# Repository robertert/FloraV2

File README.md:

# Doniczka-robot

Autonomiczna, solarna, mobilna doniczka: jezdzi po trawniku za sloncem, mierzy
warunki i sama podlewa rosline. Praca inzynierska AGH, termin styczen 2027.

## Uklad repozytorium

Jedno repo, dwie jednostki polaczone UART-em przez maszt, wspolne sterowniki.

```
components/        sterowniki dzielone przez obie jednostki
  flora_board/     mapa pinow bryly + przeliczniki odometrii
  flora_motors/    naped na Cytron MDD10A (PWM + DIR)
  flora_encoders/  enkodery kwadraturowe na PCNT
  flora_ina226/    pomiar pradu i napiecia szyny 12V
  flora_msgs/      kontrakt wiadomosci UART (wspolny dla obu stron)
hub/               BRYLA: ESP32-S3 DevKitC-1 N16R8
                   naped, odometria, zasilanie, podlewanie, telemetria
node/              GLOWICA MASZTU: ESP32-S3 z gniazdem kamery (do kupienia)
                   kompas sloneczny, BME280, IMU, czujnik deszczu
```

Nazwy katalogow `hub` i `node` pochodza z wczesniejszej wersji projektu.
`hub` to jednostka DOLNA, `node` to GLOWICA.

Wspolne komponenty trafiaja do obu projektow przez `EXTRA_COMPONENT_DIRS`
ustawione w `CMakeLists.txt` kazdej jednostki.

## Wymagania

ESP-IDF **v6.1**, zainstalowane przez EIM w `~/.espressif/v6.1/esp-idf`.
Obie jednostki to ESP32-S3.

## Praca z projektem

`./dev.sh` sam wciaga srodowisko ESP-IDF i wykrywa port, wiec nie trzeba
niczego sourcowac:

```sh
./dev.sh hub build      # zbuduj bryle
./dev.sh hub fm         # build + flash + monitor, najczestszy cykl
./dev.sh hub monitor    # sama konsola, wyjscie Ctrl+]
./dev.sh hub menuconfig
./dev.sh ports          # co widac na USB
./dev.sh help           # pelna lista komend
```

Nieznane komendy leca wprost do `idf.py`, np. `./dev.sh hub partition-table`.

Przy dwoch podlaczonych plytkach trzeba wskazac port:
`FLORA_PORT=/dev/cu.usbmodem101 ./dev.sh hub fm`.

## Debug przez MQTT

Bryla publikuje wszystko, co do niej dociera (wlasne czujniki i wiadomosci
glowicy), pod `flora/robot1/tele/*` i `flora/robot1/head/*`, a komendy
przyjmuje z `flora/robot1/cmd/*` (opis w `hub/main/hub_remote.h`).

1. Broker na Macu (`brew install mosquitto`):
   `mosquitto -c tools/dashboard/mosquitto.conf -v`
2. Adres brokera dla robota to IP Maca w tej samej sieci:
   `FLORA_MQTT_URI_DEFAULT` w `flora_board.h` albo klucz `mqtt_uri` w NVS.
3. Panel: otworz `tools/dashboard/index.html` w przegladarce, adres
   `ws://<ip-maca>:9001`. Strzalki na klawiaturze jada, spacja to STOP.
4. Z terminala: `mosquitto_sub -t 'flora/robot1/#' -v`,
   `mosquitto_pub -t flora/robot1/cmd/pump -m on`.

Naped z panelu staje sam po 1,5 s bez odswiezenia komendy (dead-man),
wiec zerwane WiFi nie zostawi jadacego robota.

**Do jakiego brokera laczy sie robot** - po kolei, az ktorys odpowie:

1. ustawienia z NVS (zmieniane zdalnie, patrz nizej),
2. serwer wkompilowany w firmware (`FLORA_MQTT_URI_DEFAULT` w `flora_board.h`,
   TLS, login `robot1`, haslo z NVS - w kodzie go nie ma),
3. broker na Macu po nazwie mDNS (`Roberts-MacBook-Pro.local`), bez hasel.

Haslo brokera trzeba wpisac raz (`cmd/config/mqtt_pass`, z lokalnego panelu,
gdy robot jest na brokerze Maca). Przezywa zwykle flashowanie, znika dopiero
po `erase-flash`.

**Ustawienia zdalnie** (karta "Ustawienia" w panelu albo z terminala), zapis
do NVS, siec i broker dzialaja po restarcie:

```sh
mosquitto_pub -t flora/robot1/cmd/config/mqtt_uri -m mqtt://172.20.10.14:1883
mosquitto_pub -t flora/robot1/cmd/reboot -m 1
```

Klucze: `wifi_ssid`, `wifi_pass`, `mqtt_uri`, `mqtt_user`, `mqtt_pass`,
`soil_dry`, `soil_wet`; wartosc `-` kasuje ustawienie. Zly adres albo haslo
w NVS nie wymaga podlaczania kabla - robot przejdzie do kolejnych prob.

**Diagnostyka zdalna** (`hub/main/hub_diag.c`):

- `tele/log` - ostrzezenia i bledy z logu ESP (poziomy W i E). Kolejka
  trzyma je takze bez polaczenia, wiec bledy z uruchamiania i z przerwy w
  sieci wychodza po polaczeniu. Konsola USB dostaje wszystko jak dotad.
- `tele/boot` (retain) - wersja firmware, data budowania, powod ostatniego
  restartu (`panic`, `task_wdt`, `brownout`... = awaria) i licznik startow.

Wersja firmware pochodzi z tagu `hub-vX.Y.Z` (`git tag hub-v0.1.0`); bez
niego jest skrot commita. Tagi `server-v...` sa dla serwera i do firmware
nie trafiaja.

**Historia** (Telegraf + InfluxDB + Grafana w Dockerze):

```sh
cd tools/telemetry && docker compose up -d
```

Grafana pod http://localhost:3001 (admin / flora-admin), dashboard
"Flora robot". Wersja na serwer (broker z TLS i haslami, Grafana i
panel za HTTPS): `tools/server/README.md`. Hasla domyslne sa tylko do laptopa - na serwer ustaw wlasne
w `tools/telemetry/.env` (`INFLUX_PASSWORD`, `INFLUX_TOKEN`, `GRAFANA_PASSWORD`).

## Aktualizacja przez siec (OTA)

Bryla ma dwa sloty aplikacji (`hub/partitions.csv`). Nowa wersja laduje do
wolnego, a stara zostaje jako zapas:

1. `git tag hub-v1.2.0 && git push origin hub-v1.2.0` - CI buduje firmware i
   wrzuca go na serwer (`tools/server/README.md`, sekcja OTA).
2. Panel, karta "Aktualizacja (OTA)": "aktualizuj do najnowszej" albo
   konkretna wersja. Naped i pompka musza stac.
3. Robot pobiera po HTTPS z serwera, sprawdza SHA-256 z manifestem i sie
   restartuje. Postep i wynik na `tele/ota`.
4. Nowa wersja startuje "na probe": potwierdza sie sama po minucie stabilnego
   polaczenia z brokerem. Bez polaczenia przez 5 min albo po awarii przed
   potwierdzeniem bootloader wraca do poprzedniej, a `tele/boot` pokazuje ja
   w `rolled_back`.

Tablicy partycji nie da sie zmienic przez OTA. Zmiana `hub/partitions.csv`
oznacza flashowanie kablem. NVS lezy w tym samym miejscu co w dawnym ukladzie,
wiec przejscie na OTA nie kasuje hasla brokera ani kalibracji.

## Podglad kamery i zbieranie danych

Glowica w trybie podgladu stawia serwer HTTP i nadaje strumien MJPEG. Adres
pojawia sie w logu po starcie (`./dev.sh node monitor`):

```
http://<ip-glowicy>/      zywy obraz w przegladarce
http://<ip-glowicy>/jpg   jedna klatka, np. curl -o kadr.jpg http://<ip>/jpg
```

**Domyslnie obraz NIE jest dostepny przez siec.** Glowica wstaje bez WiFi i
bez serwera HTTP: obrazu nikt nie oglada, a jedynym odbiorca jest detektor
przeszkod. Radio na solarnej glowicy to najwiekszy pojedynczy pobor, a serwer
HTTP ma wyzszy priorytet niz wizja i walczy z nia o kamere (zmierzone: przy
otwartej stronie czas na klatke skakal z 233 ms na 1728 ms). Linker wyrzuca
wtedy caly stos sieciowy, wiec obraz aplikacji schodzi z 1034 kB do 398 kB.

Podglad wlacza sie przez `FLORA_HEAD_CAM_NET_DEFAULT 1` w `flora_head_board.h`
i przeflashowanie - do wycelowania kamery, zebrania klatek albo ustawienia jej
wysokosci. Wtedy dopiero dziala ponizsze:

Kamera przyjmuje JEDEN format na uruchomienie, wiec glowica ma dwa tryby i
przelacza je przez `http://<ip>/mode?v=jpeg` albo `?v=raw` (zapis do NVS i
restart, okolo dwoch sekund):

| tryb | do czego | endpointy |
|---|---|---|
| `jpeg` | celowanie kamery, ocena ostrosci | `/stream`, `/jpg` |
| `raw` | zbieranie zbioru, 320x240 RGB565 | `/raw` |

Zbior zbieramy w trybie **raw**, nie JPEG: kompresja podprobkowuje chrominancje
4:2:0 i doklada artefakty blokow, czyli psuje dokladnie ten sygnal, na ktorym
stoi wykrywanie przeszkod. Prototyp na Macu musi widziec te same bajty, ktore
zobaczy pozniej algorytm na ESP.

## Narzedzia wizyjne (`tools/vision/`)

Zadnych zaleznosci z pip - sama biblioteka standardowa Pythona i `mosquitto_sub`
z brew.

```sh
# zbieranie: klatki + migawka telemetrii z MQTT do kazdej
collect.py --host 192.168.1.42 --surface kostka --light slonce --raw
collect.py --host 192.168.1.42 --surface beton --light cien --raw --no-mqtt

# prototyp wykrywania: nakladka PNG + linia JSON na klatke
ground.py data/20261101-kostka-slonce/*.rgb565

# syntetyczne klatki o znanej odpowiedzi, do testow bez kamery
synth.py /tmp/test.rgb565 --joints --shadow 90 --obstacle -50,80,24
```

`ground.py` pracuje na siatce POLARNEJ wokol srodka kadru, bo kamera patrzy
prosto w dol: PIERSCIEN to odleglosc (0 najblizej), WYCINEK to kierunek
(16 sztuk, od lewej do prawej, jak `sectors[]` w kontrakcie). W wyniku `12`
znaczy czysto do konca zasiegu, a `-1` nieznane. Przelacznik `--grid` rysuje
granice i numery wycinkow wprost na kadrze - bez tego trzeba liczyc wycinki
palcem po ekranie. Sesje lezą w `tools/vision/data/` i NIE sa w repo.

## Wykrywanie przeszkod

Glowica liczy 16 odleglosci i wysyla je w dol jako `FLORA_MSG_OBSTACLES`
(`components/flora_ground` plus `node/main/head_obstacles.c`, 4 Hz). Bryla
publikuje je na `head/obstacles`.

Nie uczymy sie, jak wyglada przeszkoda - w kazdej klatce od nowa uczymy sie,
jak wyglada PODLOZE tuz przy kamerze, i szukamy, gdzie przestaje tak wygladac.
Dlatego to samo dziala na kostce, betonie i trawie bez zadnego uczenia.
Porownanie idzie po BARWIE, nie po jasnosci, zeby cien nie byl przeszkoda.

Zanim sektory zaczna niesc centymetry, trzeba zmierzyc wysokosc obiektywu nad
ziemia i wpisac ja w `FLORA_HEAD_CAM_HEIGHT_MM`. Bez tego ida jako "nie wiem".

Rdzen algorytmu nie zalezy od ESP-IDF i kompiluje sie zwyklym gcc, co sluzy
do sprawdzania, czy wersja na robocie liczy to samo co prototyp:

```sh
cd components/flora_ground/host
cc -O2 -I../include -o runner runner.c ../flora_ground.c -lm
./runner --r-in 2 ../../../tools/vision/data/<sesja>/*.rgb565
```

Po KAZDEJ zmianie algorytmu porownaj wynik z `tools/vision/ground.py` na tych
samych klatkach. Uwaga: harness NIE wykryje bledow pamieci, bo na komputerze
stos ma megabajty - tak przeszlo przepelnienie stosu, ktore na ESP wywalalo
zadanie po dwoch sekundach.

## Stan

Bryla ma sterowniki napedu, enkoderow i pomiaru pradu, telemetrie MQTT i
zdalne sterowanie z panelu. Glowica ma petle czujnikow (fuzja kursu, kompas
sloneczny, BME280), oba lacza UART i kamere OV5640 z obiektywem 160 stopni
patrzaca w dol z masztu, na razie w trybie podgladu. Wykrywanie przeszkod jest
w planie: kontrakt `FLORA_MSG_OBSTACLES` i publikacja na MQTT juz istnieja,
brakuje producenta w glowicy i weta napedu w bryle.

**Uwaga przy uruchamianiu testu napedu: kola musza byc w powietrzu.**

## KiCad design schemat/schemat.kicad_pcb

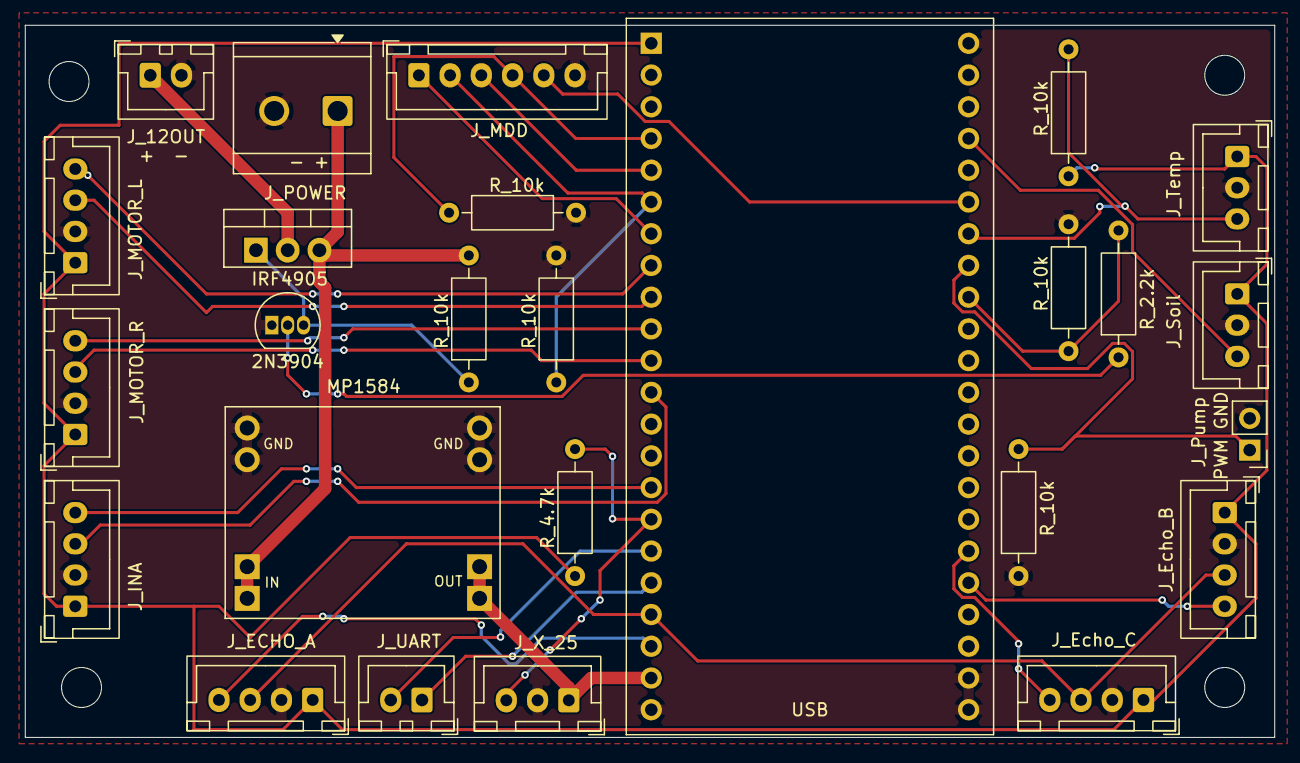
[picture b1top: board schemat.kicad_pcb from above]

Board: 2 copper layers, 100.0 x 57.0 mm, 26 parts (0 on the bottom side), 29 nets.

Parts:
J2: INA JSX; JST_XH_B4B-XH-A_1x04_P2.50mm_Vertical
J3: JSX_Motor_L; JST_XH_B4B-XH-A_1x04_P2.50mm_Vertical
J4: JSX_MDD; JST_XH_B6B-XH-A_1x06_P2.50mm_Vertical
J5: JSX_Motor_R; JST_XH_B4B-XH-A_1x04_P2.50mm_Vertical
J6: JSX_Temp; JST_XH_B3B-XH-A_1x03_P2.50mm_Vertical
J7: 12VOUT; JST_XH_B2B-XH-A_1x02_P2.50mm_Vertical
J8: JSX_ECHO_A; JST_XH_B4B-XH-A_1x04_P2.50mm_Vertical
J9: JSX_ECHO_B; JST_XH_B4B-XH-A_1x04_P2.50mm_Vertical
J10: JSX_ECHO_C; JST_XH_B4B-XH-A_1x04_P2.50mm_Vertical
J11: JSX-X25; JST_XH_B3B-XH-A_1x03_P2.50mm_Vertical
J12: JSX_Soil; JST_XH_B3B-XH-A_1x03_P2.50mm_Vertical
J13: Conn_01x02; TerminalBlock_CUI_TB007-508-02_1x02_P5.08mm_Horizontal
J14: JSX_UART; JST_XH_B2B-XH-A_1x02_P2.50mm_Vertical
J15: Pump-mosfet-Pins; PinHeader_1x02_P2.54mm_Vertical
Q1: IRF4905; TO-220-3_Vertical
Q2: 2N3904; TO-92_Inline
R1, R2, R4, R6, R7, R8: R 10k; R_Axial_DIN0207_L6.3mm_D2.5mm_P10.16mm_Horizontal
R3: R 2,2k; R_Axial_DIN0207_L6.3mm_D2.5mm_P10.16mm_Horizontal
R5: R 4,7k; R_Axial_DIN0207_L6.3mm_D2.5mm_P10.16mm_Horizontal
U2: ESP32-S3-DevKitC-1
U3: MP1584; MP1584_Module

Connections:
+3.3V: J2.1, J3.1, J5.1, J6.1, J8.1, J9.1, J10.1, J12.1, R4.1, R5.1, U2.1 (3V3)
+5V: J11.1, U2.21 (5V), U3.3 (OUT+)
+12V: J13.1, Q1.3 (S), R2.2, U3.1 (IN+)
GND: J2.2, J3.2, J4.6, J5.2, J6.2, J7.2, J8.2, J9.2, J10.2, J11.2, J12.2, J13.2, J15.2, Q2.1 (E), R1.2, R6.2, R7.2, R8.1, U2.22 (GND), U2.23 (GND), U2.43 (GND), U2.44 (GND), U3.2 (IN-), U3.4 (OUT-)
unnamed: J2.3, U2.12 (GPIO8)
unnamed: J2.4, U2.15 (GPIO9)
unnamed: J3.3, U2.9 (GPIO16)
unnamed: J3.4, U2.8 (GPIO15)
unnamed: J4.1, U2.7 (GPIO7)
unnamed: J4.2, R6.1, U2.6 (GPIO6)
unnamed: J4.3, U2.5 (GPIO5)
unnamed: J4.4, R7.1, U2.4 (GPIO4)
unnamed: J4.5, U2.28 (GPIO42)
unnamed: J5.3, U2.11 (GPIO18)
unnamed: J5.4, U2.10 (GPIO17)
unnamed: J6.3, R4.2, U2.29 (GPIO41)
unnamed: J7.1, Q1.2 (D)
unnamed: J8.4, U2.20 (GPIO14)
unnamed: J9.4, U2.40 (GPIO21)
unnamed: J8.3, J9.3, J10.3, U2.19 (GPIO13)
unnamed: J10.4, U2.39 (GPIO47)
unnamed: J11.3, R5.2, U2.16 (GPIO10)
unnamed: J12.3, U2.26 (GPIO1)
unnamed: J14.1, U2.18 (GPIO12)
unnamed: J14.2, U2.17 (GPIO11)
unnamed: J15.1, R8.2, U2.30 (GPIO40)
unnamed: Q1.1 (G), Q2.3 (C), R2.1
unnamed: Q2.2 (B), R3.1
unnamed: R1.1, R3.2, U2.31 (GPIO39)
